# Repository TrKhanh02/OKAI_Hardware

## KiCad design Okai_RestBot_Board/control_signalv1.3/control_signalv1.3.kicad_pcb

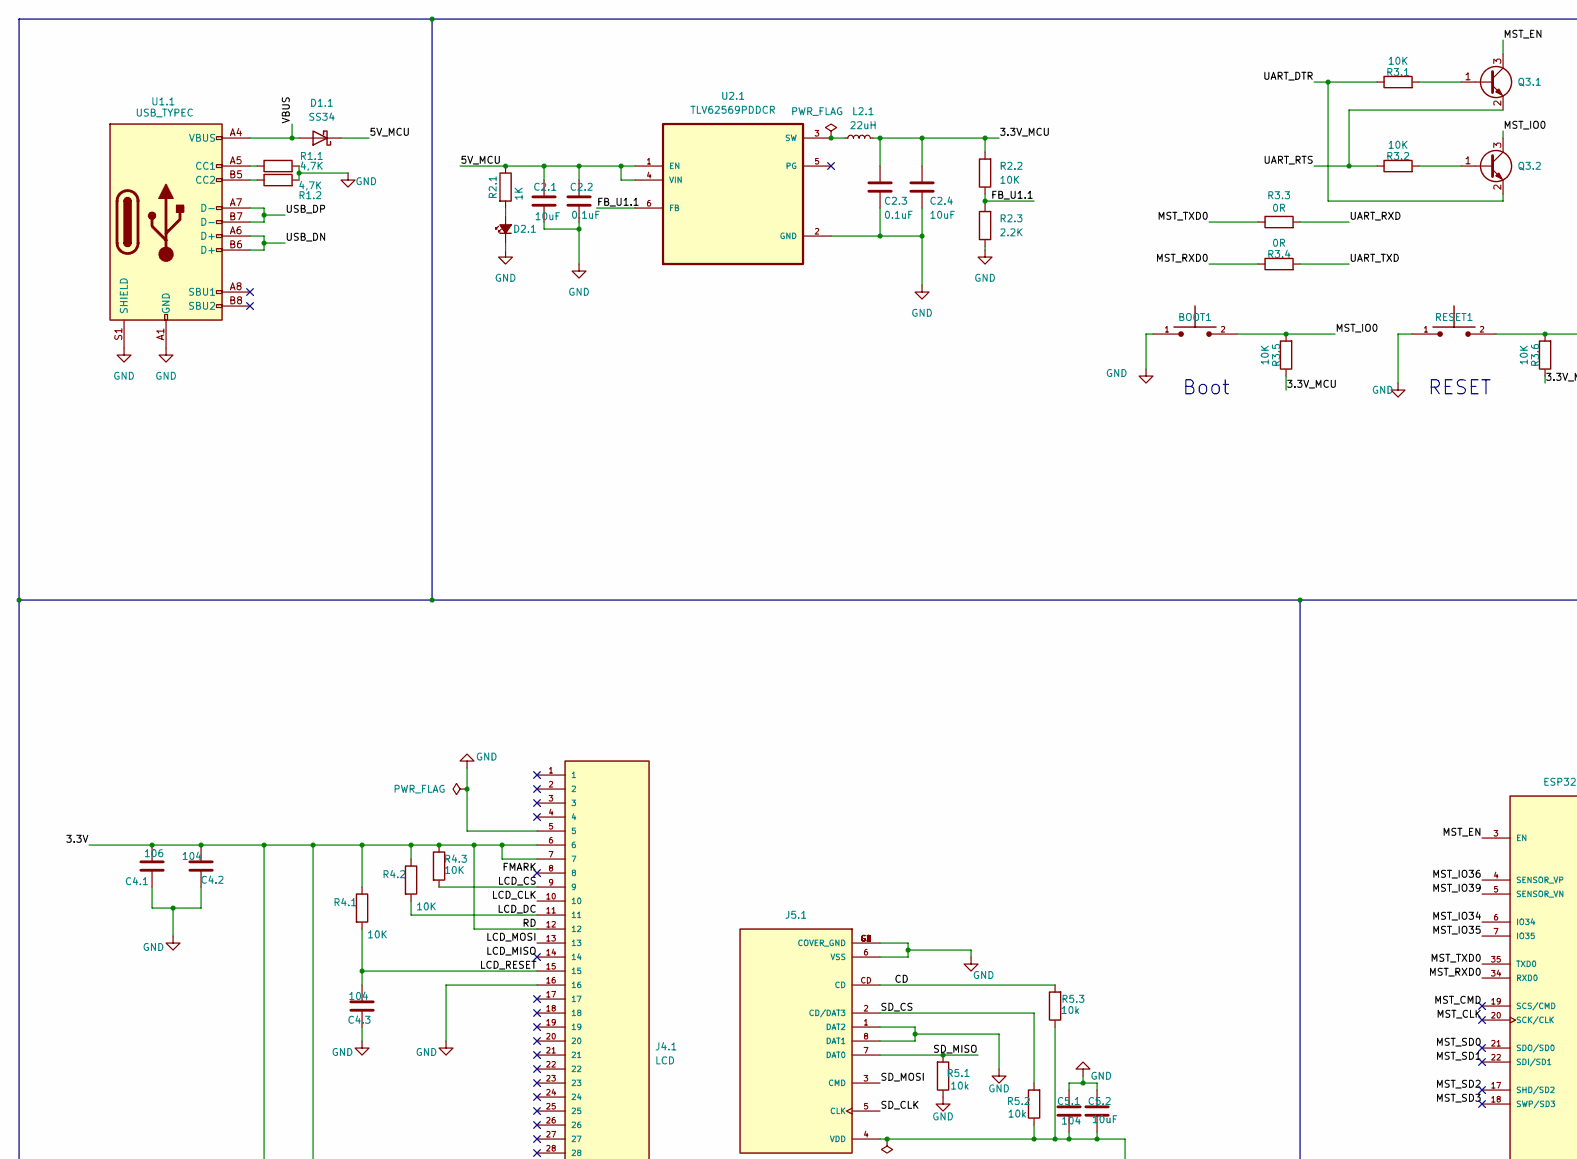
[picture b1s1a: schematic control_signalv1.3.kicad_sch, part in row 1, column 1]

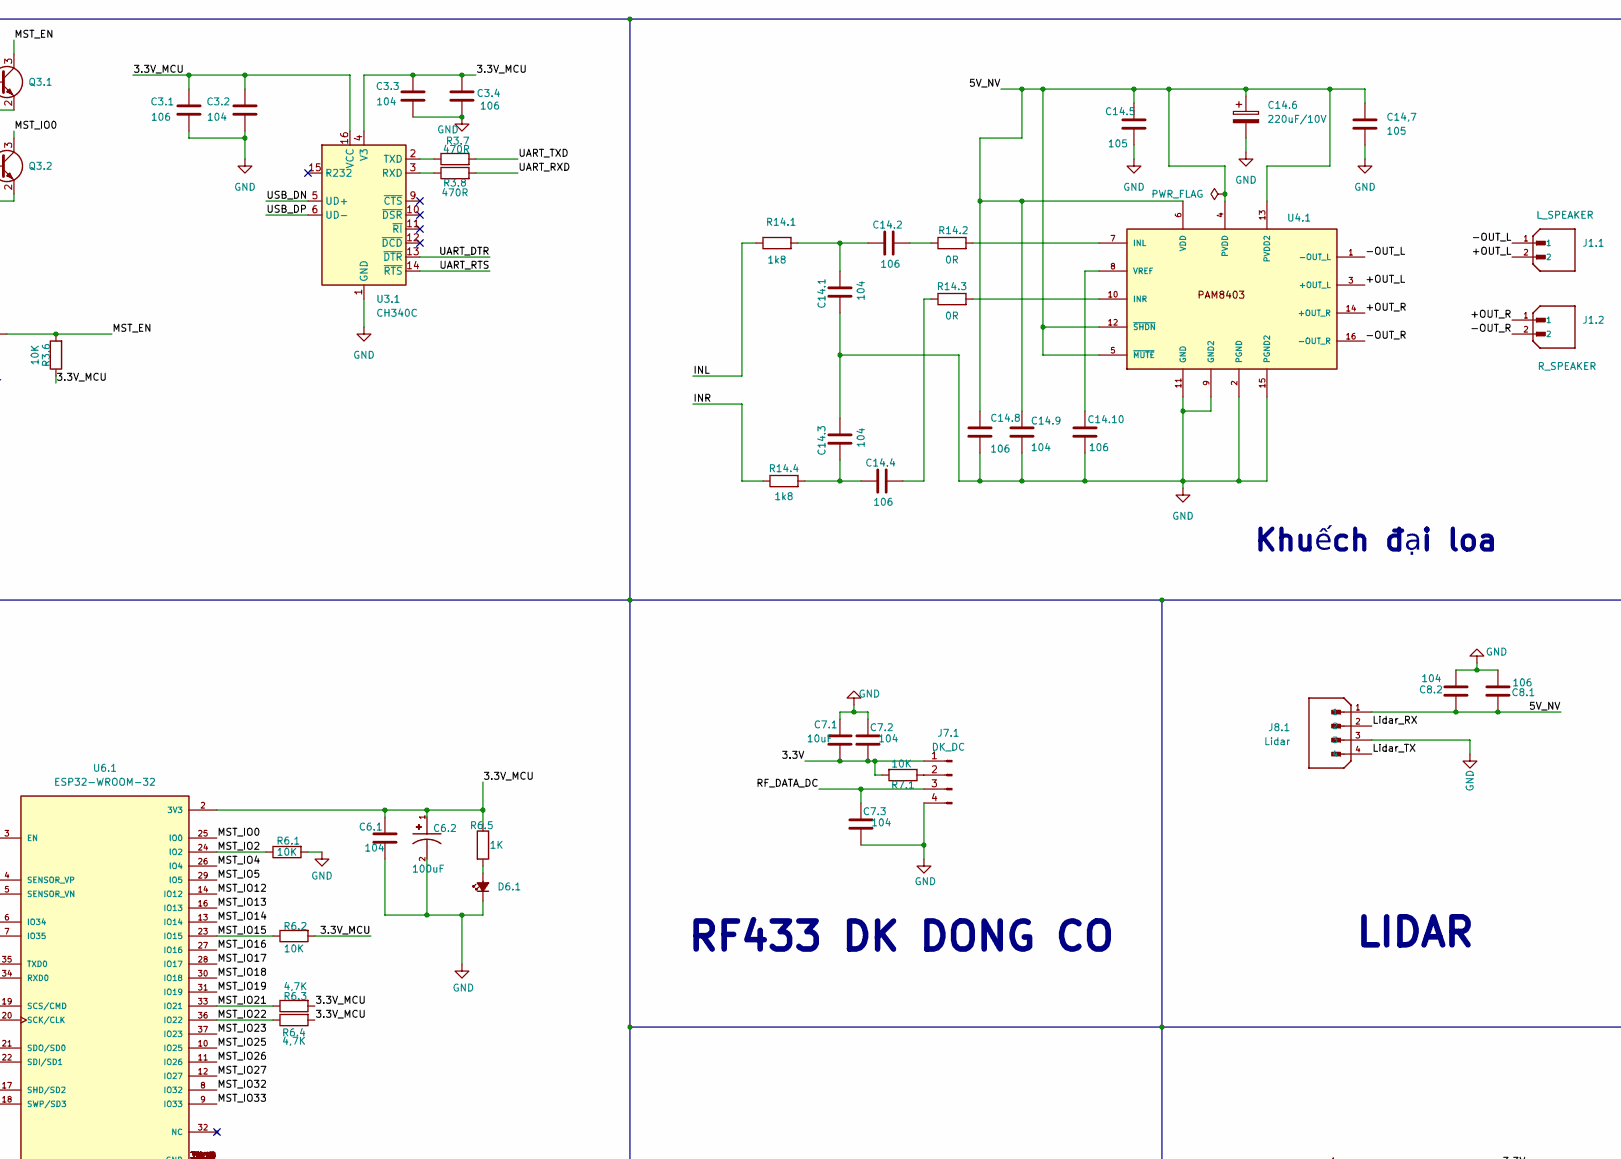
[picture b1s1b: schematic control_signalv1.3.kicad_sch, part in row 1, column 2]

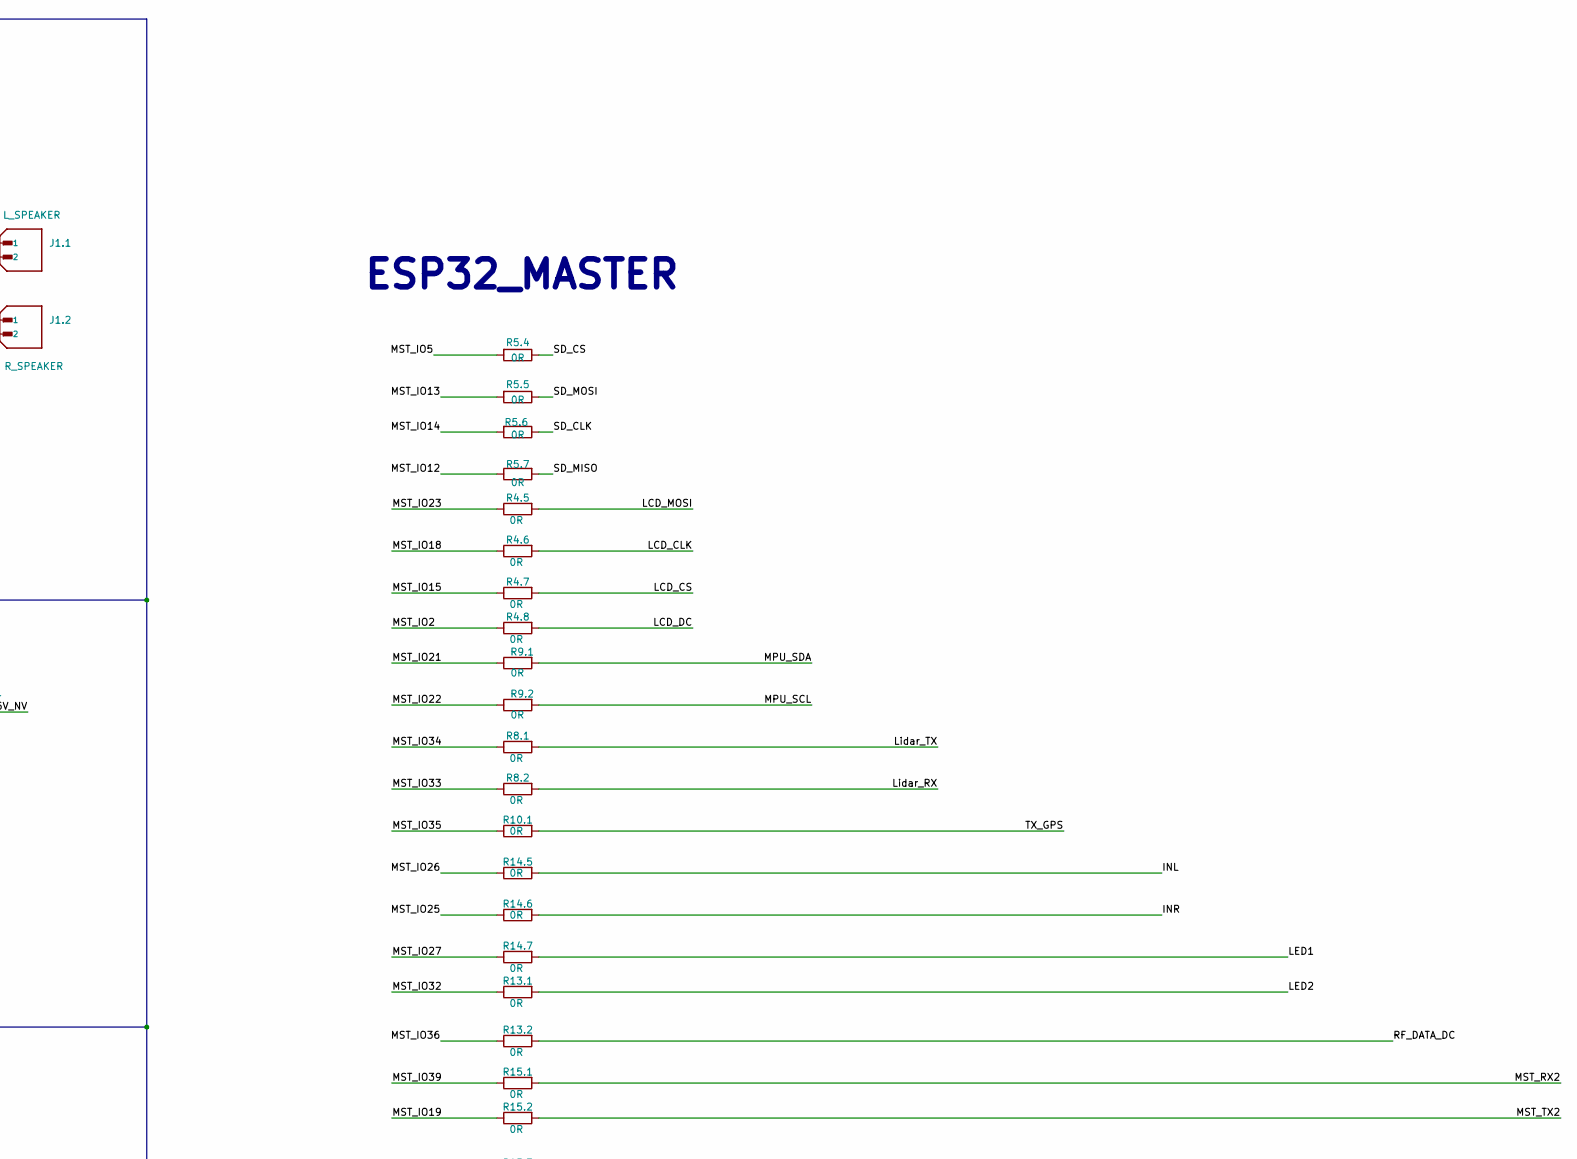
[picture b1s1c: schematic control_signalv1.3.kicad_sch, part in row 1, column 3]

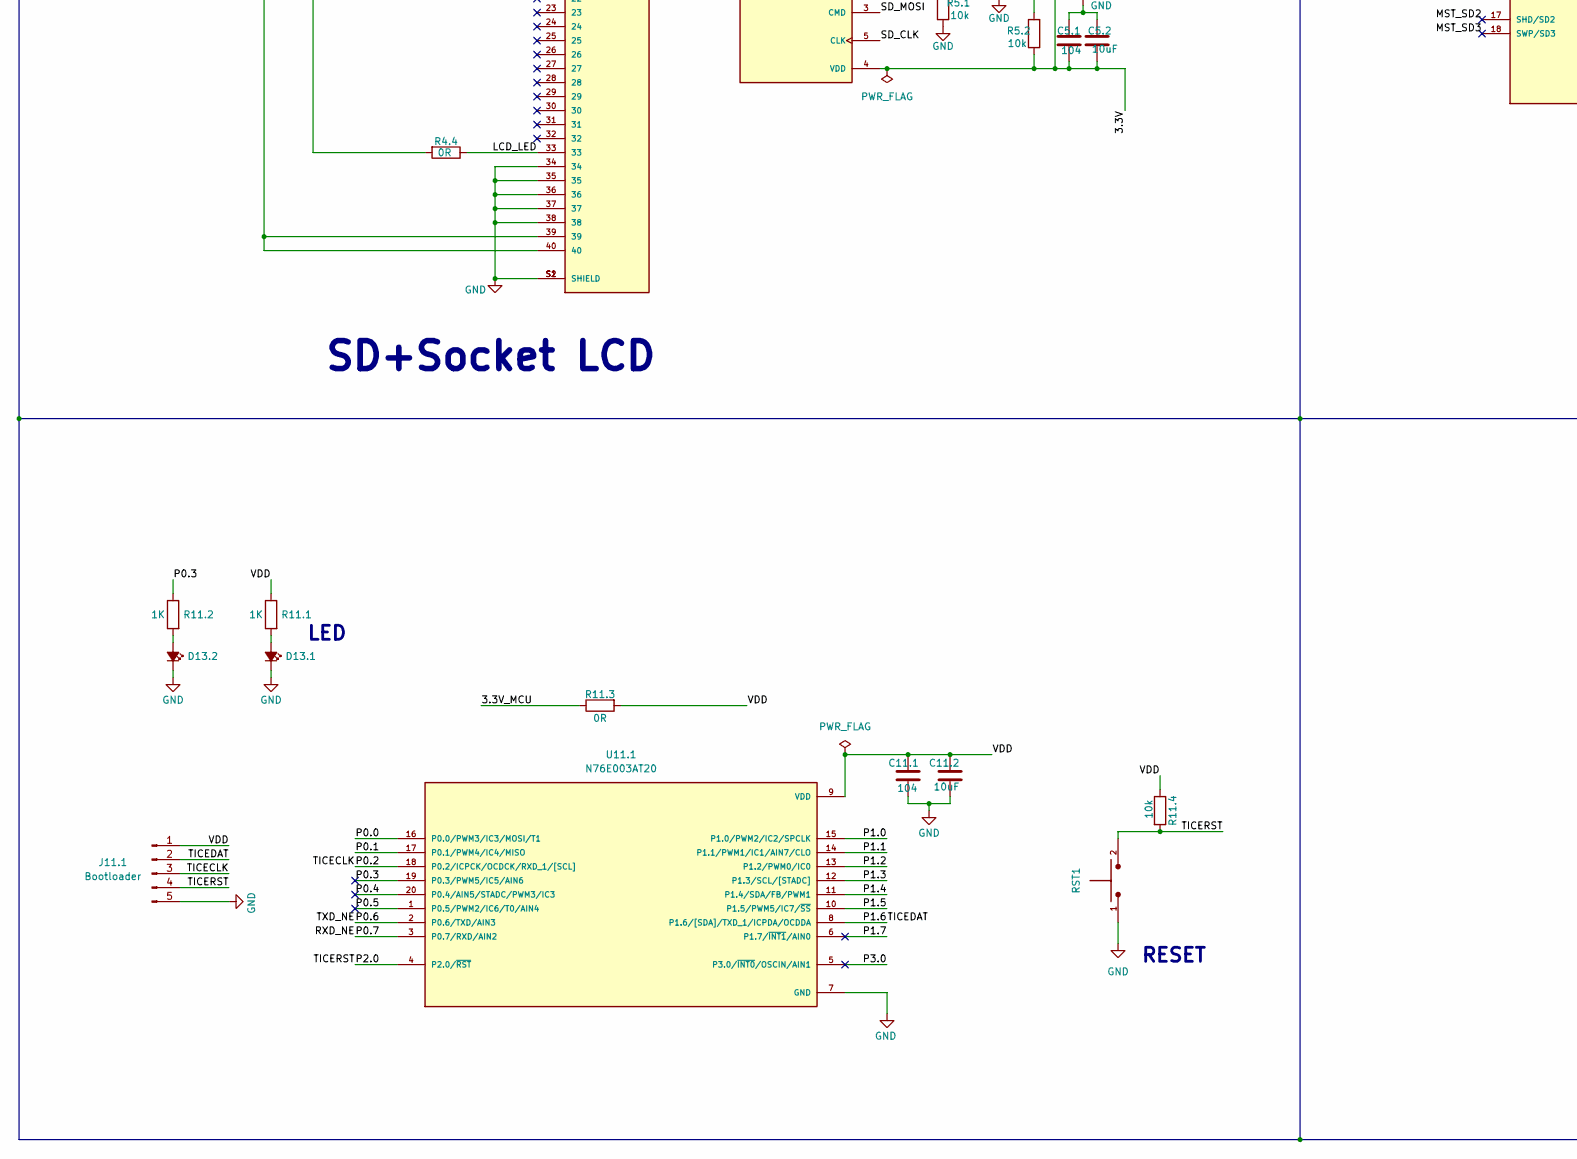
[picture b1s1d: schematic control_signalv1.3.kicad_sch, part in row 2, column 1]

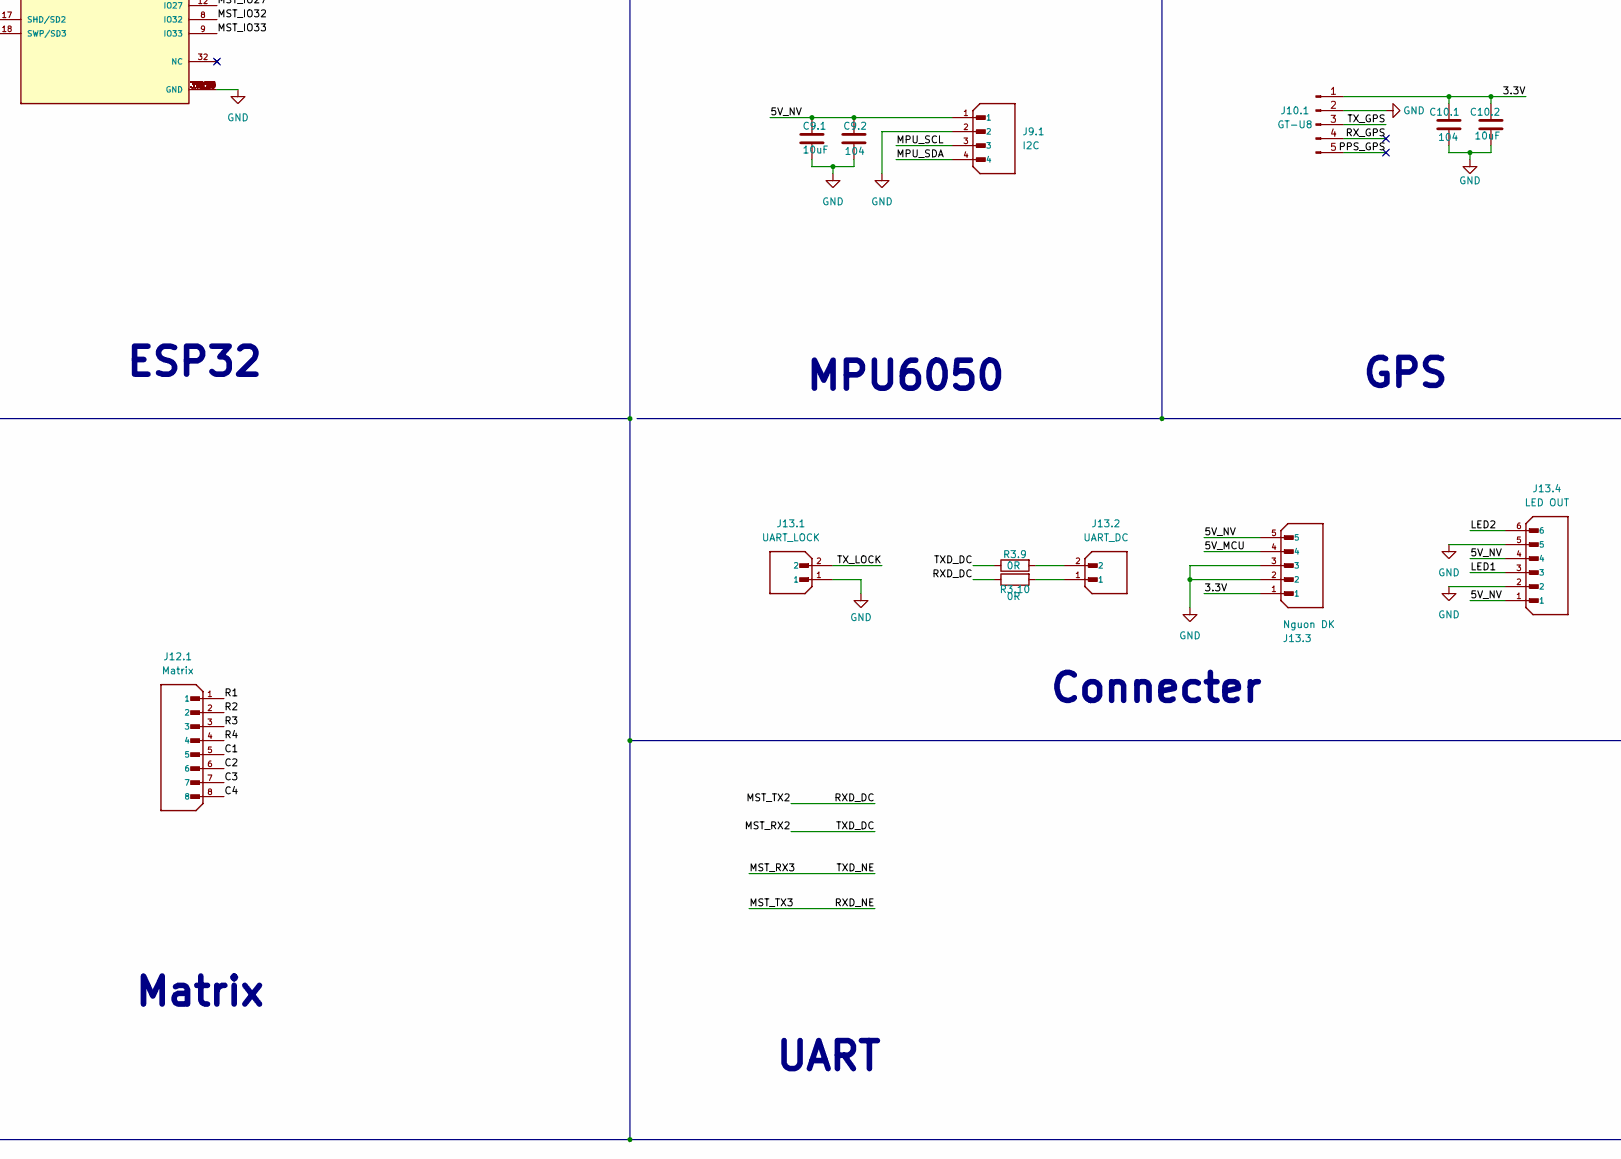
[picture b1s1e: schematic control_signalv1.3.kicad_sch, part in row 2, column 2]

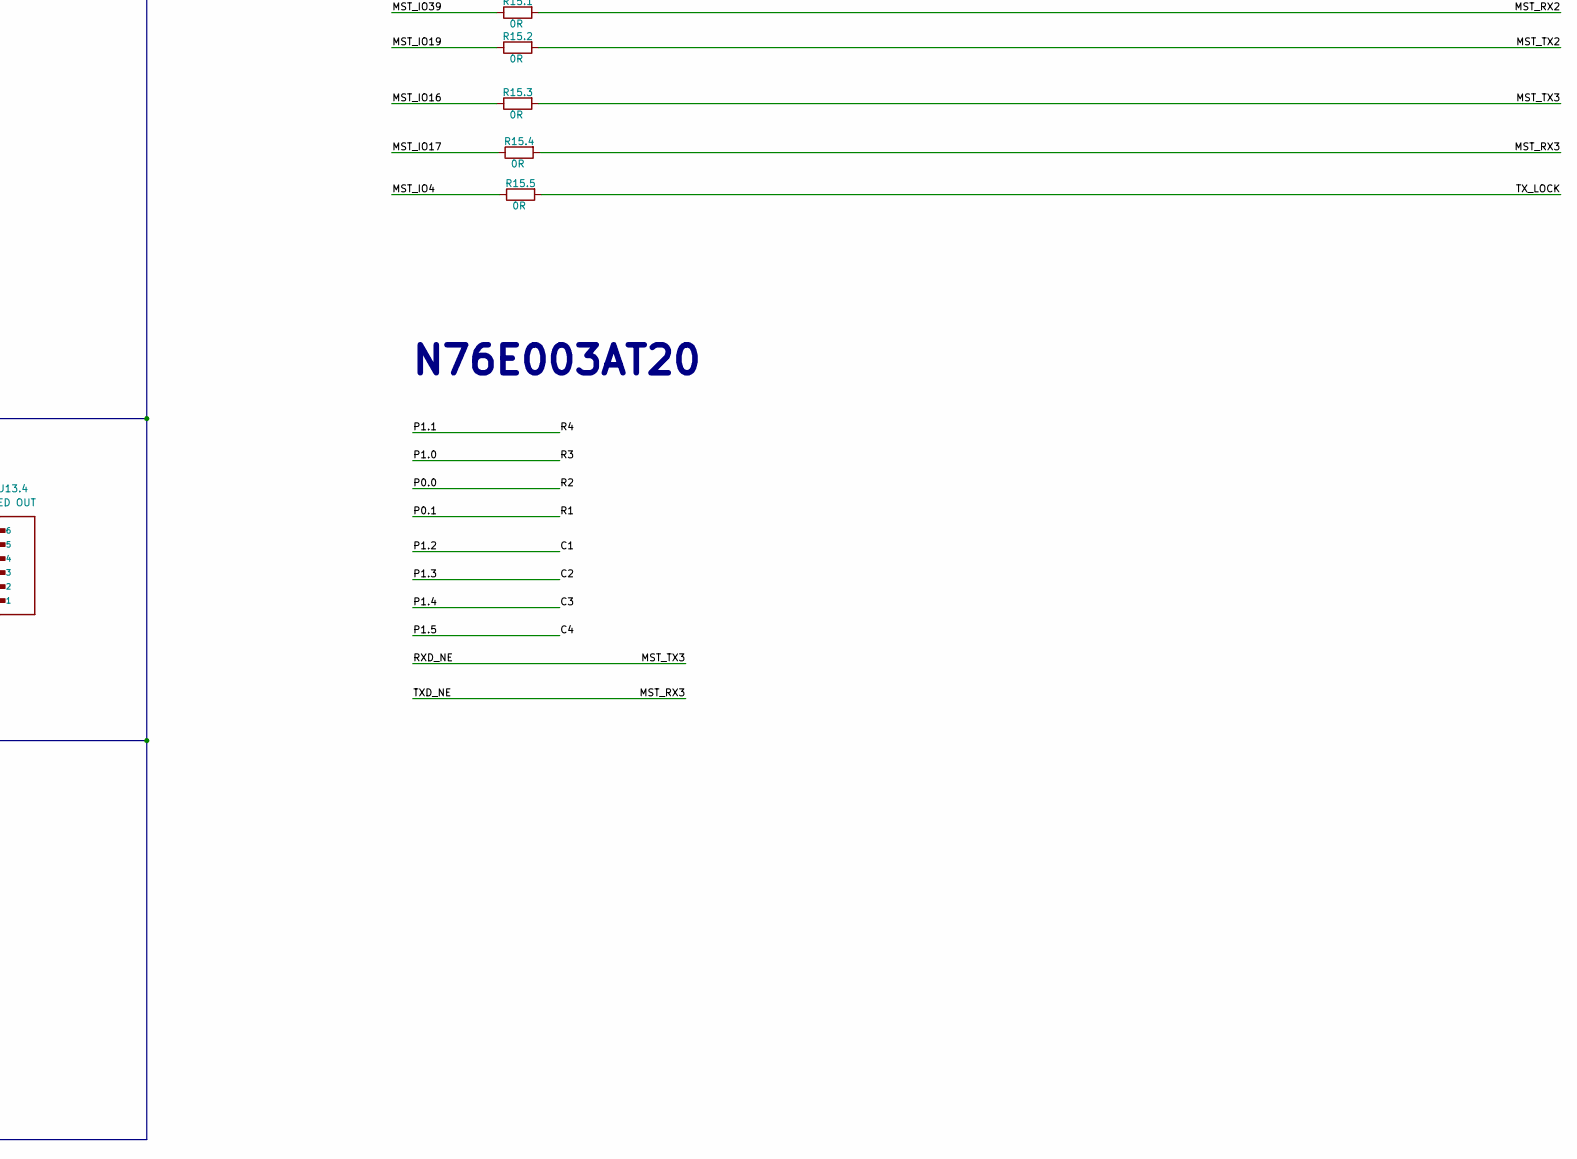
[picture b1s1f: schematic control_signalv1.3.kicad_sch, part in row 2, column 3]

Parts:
BOOT1: TS10-63-26-BE-250-SMT-TR; SW_TS10-63-26-BE-250-SMT-TR; PARTREV 1.0
C2.1, C2.4: 10uF; C_0805_2012Metric
C2.2, C2.3: 0.1uF; C_0805_2012Metric
C3.1, C3.4, C4.1, C8.1: 106; C_0805_2012Metric_Pad1.18x1.45mm_HandSolder
C3.2, C3.3, C4.2, C4.3, C5.1, C6.1, C7.2, C7.3, C8.2, C9.2, C10.1, C11.1: 104; C_0805_2012Metric_Pad1.18x1.45mm_HandSolder
C5.2, C7.1, C9.1, C10.2, C11.2: 10uF; C_0805_2012Metric_Pad1.18x1.45mm_HandSolder
C6.2: 100uF; CAPMP3216X180N; PARTREV 031320
C14,7, C14.5: 105; C_0805_2012Metric
C14.1, C14.3, C14.9: 104; C_0805_2012Metric
C14.2, C14.4, C14.8, C14.10: 106; C_0805_2012Metric
C14.6: 220uF/10V; CP_Elec_6.3x5.4
D1.1: SS34; D_SMA
D2.1, D6.1, D13.1, D13.2: LED_Small_Filled; LED_0805_2012Metric_Pad1.15x1.40mm_HandSolder
J1.1: L_SPEAKER; JST_B2B-XH-A; PARTREV N/A
J1.2: R_SPEAKER; JST_B2B-XH-A; PARTREV N/A
J4.1: LCD; TE_4-1734592-0; PARTREV C
J5.1: SD; CUI_MSD-1-A; PARTREV 1.0
J7.1: DK_DC; PinSocket_1x04_P2.54mm_Vertical
J8.1: Lidar; HRS_DF14-4P-1.25H_22_
J9.1: I2C; JST_B4B-XH-A_LF__SN_; PARTREV 7/4/21
J10.1: GT-U8; PinSocket_1x05_P2.54mm_Vertical
J11.1: Bootloader; PinHeader_1x05_P2.54mm_Vertical
J12.1: Matrix; JST_B8B-XH-A_LF__SN_; PARTREV 7/4/21
J13.1: UART_LOCK; JST_B2B-XH-A_LF__SN_; PARTREV N/A
J13.2: UART_DC; JST_B2B-XH-A_LF__SN_; PARTREV N/A
J13.3: Nguon DK; JST_B5B-XH-A; PARTREV 7/4/21
J13.4: LED OUT; JST_B6B-XH-A_LF__SN_; PARTREV 7/4/21
L2.1: 22uH; L_Ferrocore_DLG-0705
Q3.1, Q3.2: SS8050; SOT-23
R1.1, R1.2, R6.3, R6.4: 4,7K; R_0805_2012Metric_Pad1.20x1.40mm_HandSolder
R2.1, R6.5, R11.1, R11.2: 1K; R_0805_2012Metric_Pad1.20x1.40mm_HandSolder
R2.2: 10K; R_0805_2012Metric
R2.3: 2.2K; R_0805_2012Metric
R3.1, R3.2, R3.5, R3.6, R4.1, R4.2, R4.3, R6.1, R6.2, R7.1: 10K; R_0805_2012Metric_Pad1.20x1.40mm_HandSolder
R3.3, R3.4, R3.9, R3.10, R4.4, R4.5, R4.6, R4.7, R4.8, R5.4, R5.5, R5.6, R5.7, R8.1, R8.2, R9.1, R9.2, R10.1, R11.3, R13.1, R13.2, R14.5, R14.6, R14.7, R15.1, R15.2, R15.3, R15.4, R15.5: 0R; R_0805_2012Metric_Pad1.20x1.40mm_HandSolder
R3.7, R3.8: 470R; R_0805_2012Metric_Pad1.20x1.40mm_HandSolder
R5.1, R5.2, R5.3, R11.4: 10k; R_0805_2012Metric_Pad1.20x1.40mm_HandSolder
R14.1, R14.4: 1k8; R_0805_2012Metric
R14.2, R14.3: 0R; R_0805_2012Metric
RESET1: TS10-63-26-BE-250-SMT-TR; SW_TS10-63-26-BE-250-SMT-TR; PARTREV 1.0
RST1: TS10-63-26-BE-250-SMT-TR; SW_TS10-63-26-BE-250-SMT-TR; PARTREV 1.0
U1.1: USB_TYPEC; USB_C_Receptacle_HRO_TYPE-C-31-M-12
U2.1: TLV62569PDDCR; SOT95P280X110-6N
U3.1: CH340C; SOIC-16_3.9x9.9mm_P1.27mm
U4.1: PAM8403; SOP-16
U6.1: ESP32-WROOM-32; MODULE_ESP32-WROOM-32
U11.1: N76E003AT20; SOP65P640X120-20N; PARTREV 1.04

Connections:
/3.3V: C4.1.2, C4.2.2, C5.1.1, C5.2.1, C7.1.2, C7.2.2, C10.1.1, C10.2.1, J4.1.6, J4.1.7, J4.1.12, J4.1.39, J4.1.40, J5.1.4 (VDD), J7.1.1, J10.1.1, J13.3.1, R4.1.1, R4.2.1, R4.3.1, R4.4.2, R5.2.1, R5.3.1, R7.1.2
/3.3V_MCU: C2.3.1, C2.4.1, C3.1.2, C3.2.2, C3.3.2, C3.4.2, C6.1.1, C6.2.1, L2.1.1, R2.2.2, R3.5.1, R3.6.1, R6.2.2, R6.3.2, R6.4.2, R6.5.1, R11.3.1, U3.1.4 (V3), U3.1.16 (VCC), U6.1.2 (3V3)
/5V_MCU: C2.1.1, C2.2.1, D1.1.1 (K), J13.3.4, R2.1.1, U2.1.1 (EN), U2.1.4 (VIN)
/5V_NV: C8.1.1, C8.2.1, C9.1.1, C9.2.1, C14,7.2, C14.5.2, C14.6.1, C14.8.2, C14.9.2, J8.1.1, J9.1.1, J13.3.5, J13.4.1, J13.4.4, U4.1.4 (PVDD), U4.1.5 (~MUTE), U4.1.6 (VDD), U4.1.12 (~SHDN), U4.1.13 (PVDD2)
/+OUT_L: J1.1.2, U4.1.3 (+OUT_L)
/+OUT_R: J1.2.1, U4.1.14 (+OUT_R)
/-OUT_L: J1.1.1, U4.1.1 (-OUT_L)
/-OUT_R: J1.2.2, U4.1.16 (-OUT_R)
/C1: J12.1.5, U11.1.13 (P1.2/PWM0/IC0)
/C2: J12.1.6, U11.1.12 (P1.3/SCL/[STADC])
/C3: J12.1.7, U11.1.11 (P1.4/SDA/FB/PWM1)
/C4: J12.1.8, U11.1.10 (P1.5/PWM5/IC7/~SS)
/CD: J5.1.CD, R5.3.2
/FB_U1.1: R2.2.1, R2.3.2, U2.1.6 (FB)
/FMARK: J4.1.8
/INL: R14.1.1, R14.5.2
/INR: R14.4.1, R14.6.2
/LCD_CLK: J4.1.10, R4.6.2
/LCD_CS: J4.1.9, R4.3.2, R4.7.2
/LCD_DC: J4.1.11, R4.2.2, R4.8.2
/LCD_LED: J4.1.33, R4.4.1
/LCD_MISO: J4.1.14
/LCD_MOSI: J4.1.13, R4.5.2
/LCD_RESET: C4.3.2, J4.1.15, R4.1.2
/LED1: J13.4.3, R14.7.2
/LED2: J13.4.6, R13.1.2
/Lidar_RX: J8.1.2, R8.2.2
/Lidar_TX: J8.1.4, R8.1.2
/MPU_SCL: J9.1.3, R9.2.2
/MPU_SDA: J9.1.4, R9.1.2
/MST_CLK: U6.1.20 (SCK/CLK)
/MST_CMD: U6.1.19 (SCS/CMD)
/MST_EN: Q3.1.3 (C), R3.6.2, RESET1.2, U6.1.3 (EN)
/MST_IO0: BOOT1.2, Q3.2.3 (C), R3.5.2, U6.1.25 (IO0)
/MST_IO2: R4.8.1, R6.1.1, U6.1.24 (IO2)
/MST_IO4: R15.5.1, U6.1.26 (IO4)
/MST_IO5: R5.4.2, U6.1.29 (IO5)
/MST_IO12: R5.7.1, U6.1.14 (IO12)
/MST_IO13: R5.5.2, U6.1.16 (IO13)
/MST_IO14: R5.6.2, U6.1.13 (IO14)
/MST_IO15: R4.7.1, R6.2.1, U6.1.23 (IO15)
/MST_IO16: R15.3.1, U6.1.27 (IO16)
/MST_IO17: R15.4.1, U6.1.28 (IO17)
/MST_IO18: R4.6.1, U6.1.30 (IO18)
/MST_IO19: R15.2.1, U6.1.31 (IO19)
/MST_IO21: R6.3.1, R9.1.1, U6.1.33 (IO21)
/MST_IO22: R6.4.1, R9.2.1, U6.1.36 (IO22)
/MST_IO23: R4.5.1, U6.1.37 (IO23)
/MST_IO25: R14.6.1, U6.1.10 (IO25)
/MST_IO26: R14.5.1, U6.1.11 (IO26)
/MST_IO27: R14.7.1, U6.1.12 (IO27)
/MST_IO32: R13.1.1, U6.1.8 (IO32)
/MST_IO33: R8.2.1, U6.1.9 (IO33)
/MST_IO34: R8.1.1, U6.1.6 (IO34)
/MST_IO35: R10.1.1, U6.1.7 (IO35)
/MST_IO36: R13.2.1, U6.1.4 (SENSOR_VP)
/MST_IO39: R15.1.1, U6.1.5 (SENSOR_VN)
/MST_RX2: R3.9.1, R15.1.2
/MST_RX3: R15.4.2, U11.1.2 (P0.6/TXD/AIN3)
/MST_RXD0: R3.4.1, U6.1.34 (RXD0)
/MST_SD0: U6.1.21 (SDO/SD0)
/MST_SD1: U6.1.22 (SDI/SD1)
/MST_SD2: U6.1.17 (SHD/SD2)
/MST_SD3: U6.1.18 (SWP/SD3)
/MST_TX2: R3.10.1, R15.2.2
/MST_TX3: R15.3.2, U11.1.3 (P0.7/RXD/AIN2)
/MST_TXD0: R3.3.1, U6.1.35 (TXD0)
/P0.0: J12.1.2, U11.1.16 (P0.0/PWM3/IC3/MOSI/T1)
/P0.1: J12.1.1, U11.1.17 (P0.1/PWM4/IC4/MISO)
/P0.2: J11.1.3, U11.1.18 (P0.2/ICPCK/OCDCK/RXD_1/[SCL])
/P0.3: R11.2.1, U11.1.19 (P0.3/PWM5/IC5/AIN6)
/P0.4: U11.1.20 (P0.4/AIN5/STADC/PWM3/IC3)
/P0.5: U11.1.1 (P0.5/PWM2/IC6/T0/AIN4)
/P1.0: J12.1.3, U11.1.15 (P1.0/PWM2/IC2/SPCLK)
/P1.1: J12.1.4, U11.1.14 (P1.1/PWM1/IC1/AIN7/CLO)
/P1.6: J11.1.2, U11.1.8 (P1.6/[SDA]/TXD_1/ICPDA/OCDDA)
/P1.7: U11.1.6 (P1.7/~INT1/AIN0)
/P2.0: J11.1.4, R11.4.2, RST1.2, U11.1.4 (P2.0/~RST)
/P3.0: U11.1.5 (P3.0/~INT0/OSCIN/AIN1)
/PPS_GPS: J10.1.5
/RF_DATA_DC: C7.3.1, J7.1.3, R13.2.2
/RX_GPS: J10.1.4
/SD_CLK: J5.1.5 (CLK), R5.6.1
/SD_CS: J5.1.2 (CD/DAT3), R5.2.2, R5.4.1
/SD_MISO: J5.1.7 (DAT0), R5.1.2, R5.7.2
/SD_MOSI: J5.1.3 (CMD), R5.5.1
/TX_GPS: J10.1.3, R10.1.2
/TX_LOCK: J13.1.2, R15.5.2
/UART_DTR: Q3.2.2 (E), R3.1.1, U3.1.13 (~DTR)
/UART_RTS: Q3.1.2 (E), R3.2.1, U3.1.14 (~RTS)
/UART_RXD: R3.3.2, R3.8.2
/UART_TXD: R3.4.2, R3.7.2
/USB_DN: U1.1.A6 (D+), U1.1.B6 (D+), U3.1.5 (UD+)
/USB_DP: U1.1.A7 (D-), U1.1.B7 (D-), U3.1.6 (UD-)
/VBUS: D1.1.2 (A), U1.1.A4 (VBUS), U1.1.A9 (VBUS), U1.1.B4 (VBUS), U1.1.B9 (VBUS)
/VDD: C11.1.1, C11.2.1, J11.1.1, R11.1.1, R11.3.2, R11.4.1, U11.1.9 (VDD)
GND: BOOT1.1, C2.1.2, C2.2.2, C2.3.2, C2.4.2, C3.1.1, C3.2.1, C3.3.1, C3.4.1, C4.1.1, C4.2.1, C4.3.1, C5.1.2, C5.2.2, C6.1.2, C6.2.2, C7.1.1, C7.2.1, C7.3.2, C8.1.2, C8.2.2, C9.1.2, C9.2.2, C10.1.2, C10.2.2, C11.1.2, C11.2.2, C14,7.1, C14.1.2, C14.3.1, C14.5.1, C14.6.2, C14.8.1, C14.9.1, C14.10.1, D2.1.1 (K), D6.1.1 (K), D13.1.1 (K), D13.2.1 (K), J4.1.5, J4.1.16, J4.1.34, J4.1.35, J4.1.36, J4.1.37, J4.1.38, J4.1.S1 (SHIELD), J4.1.S2 (SHIELD), J5.1.1 (DAT2), J5.1.6 (VSS), J5.1.8 (DAT1), J5.1.G1 (COVER_GND), J5.1.G2 (COVER_GND), J5.1.G3 (COVER_GND), J5.1.G4 (COVER_GND), J7.1.4, J8.1.3, J9.1.2, J10.1.2, J11.1.5, J13.1.1, J13.3.2, J13.3.3, J13.4.2, J13.4.5, R1.1.2, R1.2.2, R2.3.1, R5.1.1, R6.1.2, RESET1.1, RST1.1, U1.1.A1 (GND), U1.1.A12 (GND), U1.1.B1 (GND), U1.1.B12 (GND), U1.1.S1 (SHIELD), U2.1.2 (GND), U3.1.1 (GND), U4.1.2 (PGND), U4.1.9 (GND2), U4.1.11 (GND), U4.1.15 (PGND2), U6.1.1 (GND), U6.1.15 (GND), U6.1.38 (GND), U6.1.39_1 (GND), U6.1.39_2 (GND), U6.1.39_3 (GND), U6.1.39_4 (GND), U6.1.39_5 (GND), U6.1.39_6 (GND), U6.1.39_7 (GND), U6.1.39_8 (GND), U6.1.39_9 (GND), U6.1.39_10 (GND), U6.1.39_11 (GND), U6.1.39_12 (GND), U6.1.39_13 (GND), U6.1.39_14 (GND), U6.1.39_15 (GND), U6.1.39_16 (GND), U6.1.39_17 (GND), U6.1.39_18 (GND), U6.1.39_19 (GND), U6.1.39_20 (GND), U6.1.39_21 (GND), U11.1.7 (GND)
unnamed: C14.1.1, C14.2.2, R14.1.2
unnamed: C14.2.1, R14.2.1
unnamed: C14.3.2, C14.4.2, R14.4.2
unnamed: C14.4.1, R14.3.1
unnamed: D2.1.2 (A), R2.1.2
unnamed: D6.1.2 (A), R6.5.2
unnamed: D13.1.2 (A), R11.1.2
unnamed: D13.2.2 (A), R11.2.2
unnamed: J7.1.2, R7.1.1
unnamed: J13.2.1, R3.10.2
unnamed: J13.2.2, R3.9.2
unnamed: Q3.1.1 (B), R3.1.2
unnamed: Q3.2.1 (B), R3.2.2
unnamed: R1.1.1, U1.1.A5 (CC1)
unnamed: R1.2.1, U1.1.B5 (CC2)
unnamed: L2.1.2, U2.1.3 (SW)
unnamed: R3.8.1, U3.1.3 (RXD)
unnamed: R3.7.1, U3.1.2 (TXD)
unnamed: R14.2.2, U4.1.7 (INL)
unnamed: R14.3.2, U4.1.10 (INR)
unnamed: C14.10.2, U4.1.8 (VREF)

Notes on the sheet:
Connecter
Khuếch đại loa
ESP32_MASTER
LIDAR
RF433 DK DONG CO
MPU6050
ESP32
Boot
RESET
LED
Matrix
UART
N76E003AT20
SD+Socket LCD
GPS

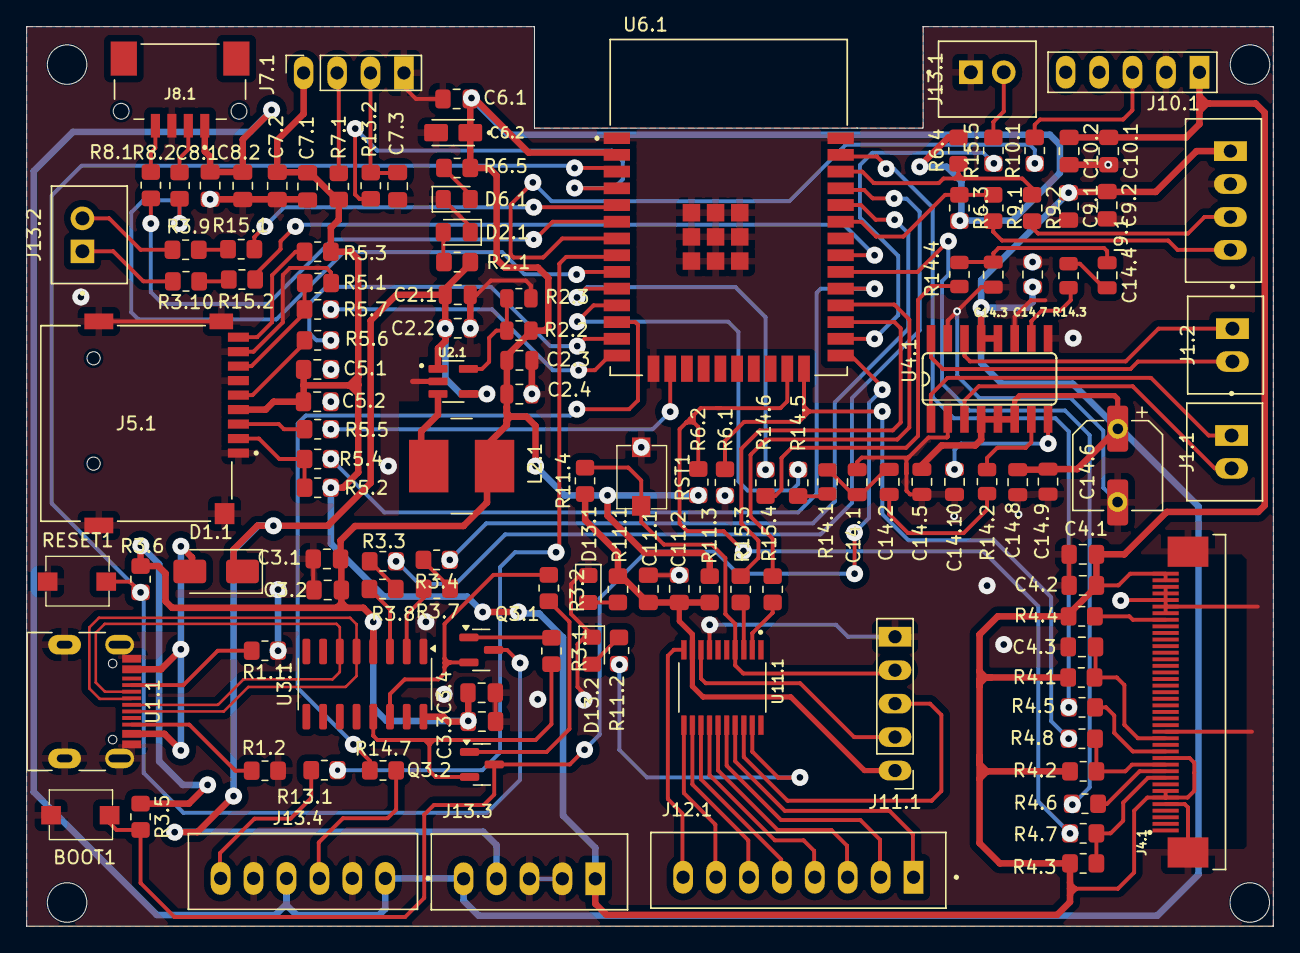
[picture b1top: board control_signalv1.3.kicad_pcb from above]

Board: 2 copper layers, 94.7 x 68.3 mm, 126 parts (0 on the bottom side), 104 nets.

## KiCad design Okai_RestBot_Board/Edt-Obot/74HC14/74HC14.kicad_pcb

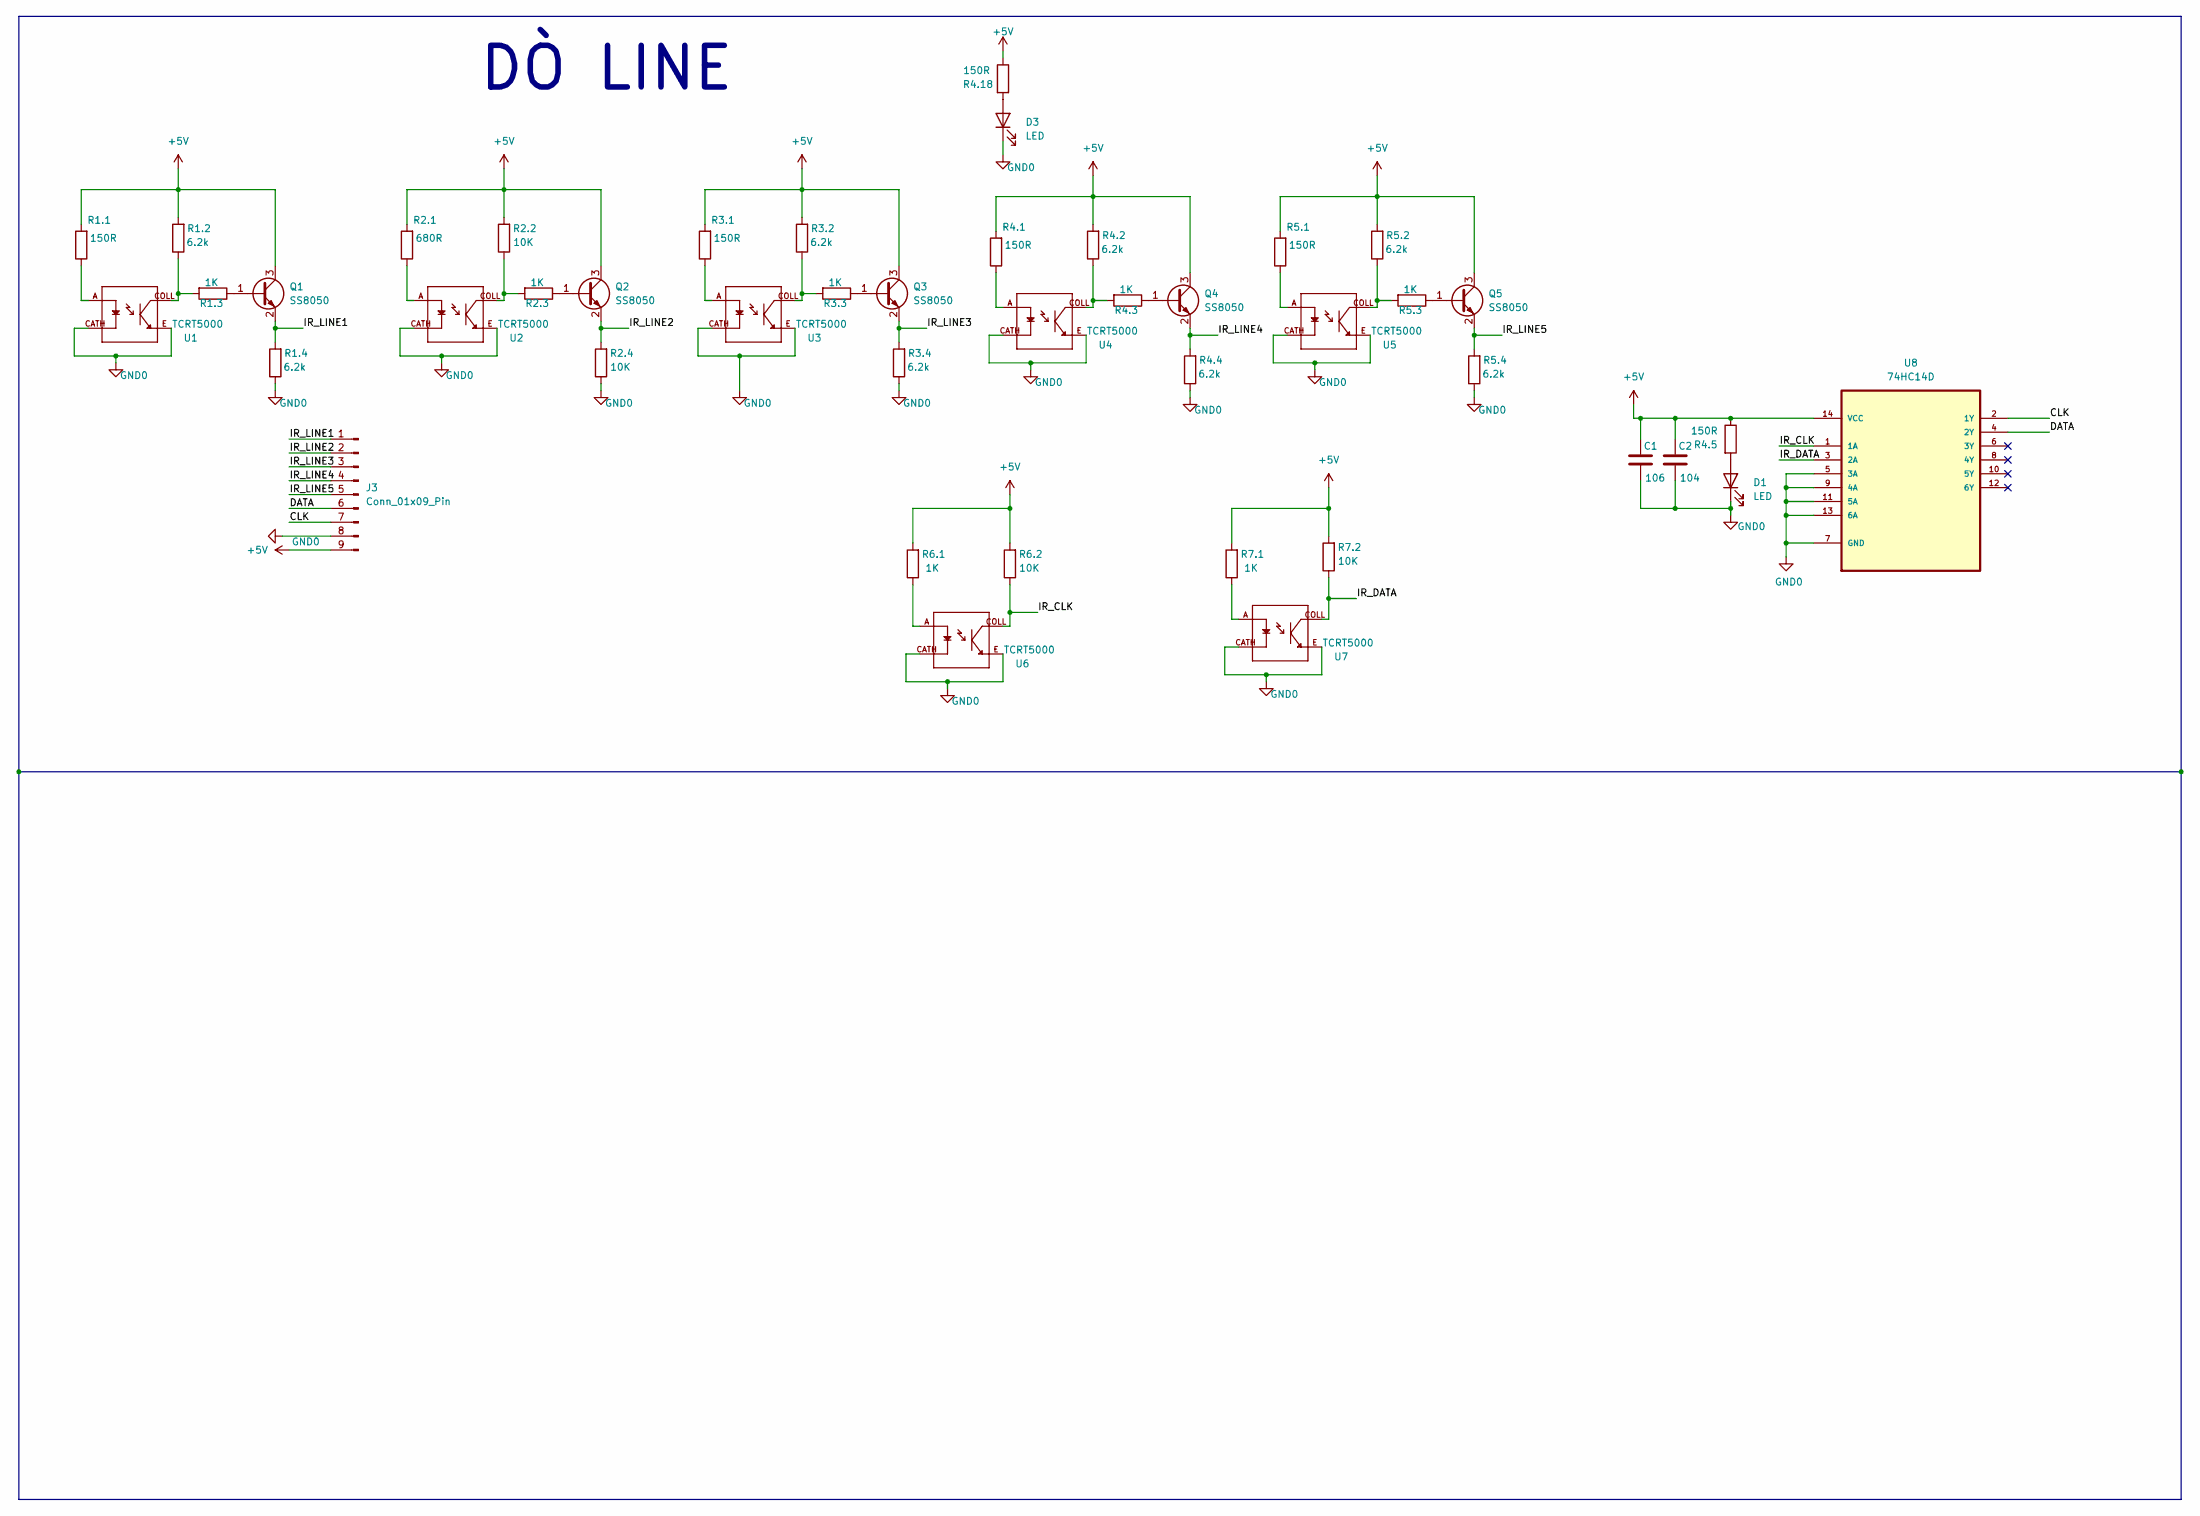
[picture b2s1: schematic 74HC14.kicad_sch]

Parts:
C1: 106; C_0805_2012Metric
C2: 104; C_0805_2012Metric
D1, D3: LED; LED_0805_2012Metric
J3: Conn_01x09_Pin; PinHeader_1x09_P2.54mm_Vertical
Q1, Q2, Q3, Q4, Q5: SS8050; SOT-23
R1.1, R3.1, R4.1, R4.5, R4.18, R5.1: 150R; R_0805_2012Metric
R1.2, R1.4, R3.2, R3.4, R4.2, R4.4, R5.2, R5.4: 6.2k; R_0805_2012Metric
R1.3, R2.3, R3.3, R4.3, R5.3, R6.1, R7.1: 1K; R_0805_2012Metric
R2.1: 680R; R_0805_2012Metric
R2.2, R2.4, R6.2, R7.2: 10K; R_0805_2012Metric
U1, U2, U3, U4, U5, U6, U7: TCRT5000; OPTO_TCRT5000; PARTREV 1.7
U8: 74HC14D; SOIC127P600X175-14N; MPN 74HC14D

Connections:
+5V: C1.2, C2.2, J3.9, Q1.3 (C), Q2.3 (C), Q3.3 (C), Q4.3 (C), Q5.3 (C), R1.1.2, R1.2.2, R2.1.2, R2.2.2, R3.1.2, R3.2.2, R4.1.2, R4.2.2, R4.5.1, R4.18.1, R5.1.2, R5.2.2, R6.1.2, R6.2.2, R7.1.2, R7.2.2, U8.14 (VCC)
/CLK: J3.7, U8.2 (1Y)
/DATA: J3.6, U8.4 (2Y)
/IR_CLK: R6.2.1, U6.COLL, U8.1 (1A)
/IR_DATA: R7.2.1, U7.COLL, U8.3 (2A)
/IR_LINE1: J3.1, Q1.2 (E), R1.4.2
/IR_LINE2: J3.2, Q2.2 (E), R2.4.2
/IR_LINE3: J3.3, Q3.2 (E), R3.4.2
/IR_LINE4: J3.4, Q4.2 (E), R4.4.2
/IR_LINE5: J3.5, Q5.2 (E), R5.4.2
GND0: C1.1, C2.1, D1.1 (K), D3.1 (K), J3.8, R1.4.1, R2.4.1, R3.4.1, R4.4.1, R5.4.1, U1.CATH, U1.E, U2.CATH, U2.E, U3.CATH, U3.E, U4.CATH, U4.E, U5.CATH, U5.E, U6.CATH, U6.E, U7.CATH, U7.E, U8.5 (3A), U8.7 (GND), U8.9 (4A), U8.11 (5A), U8.13 (6A)
unnamed: D1.2 (A), R4.5.2
unnamed: D3.2 (A), R4.18.2
unnamed: Q1.1 (B), R1.3.1
unnamed: Q2.1 (B), R2.3.1
unnamed: Q3.1 (B), R3.3.1
unnamed: Q4.1 (B), R4.3.1
unnamed: Q5.1 (B), R5.3.1
unnamed: R1.1.1, U1.A
unnamed: R1.2.1, R1.3.2, U1.COLL
unnamed: R2.1.1, U2.A
unnamed: R2.2.1, R2.3.2, U2.COLL
unnamed: R3.1.1, U3.A
unnamed: R3.2.1, R3.3.2, U3.COLL
unnamed: R4.1.1, U4.A
unnamed: R4.2.1, R4.3.2, U4.COLL
unnamed: R5.1.1, U5.A
unnamed: R5.2.1, R5.3.2, U5.COLL
unnamed: R6.1.1, U6.A
unnamed: R7.1.1, U7.A

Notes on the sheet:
DÒ LINE
